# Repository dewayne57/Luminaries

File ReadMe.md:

# Luminaries 

This project contains the software and hardware for simulated candles that operate from 12V 
(meaning they can be powered from lawn lighting) with optional CDS (Cadmium-Sulfide) photo
cell control (on at dusk off at dawn).  The software simulates a fairly large candle, like 
might be placed inside a luminary or pumpkin.

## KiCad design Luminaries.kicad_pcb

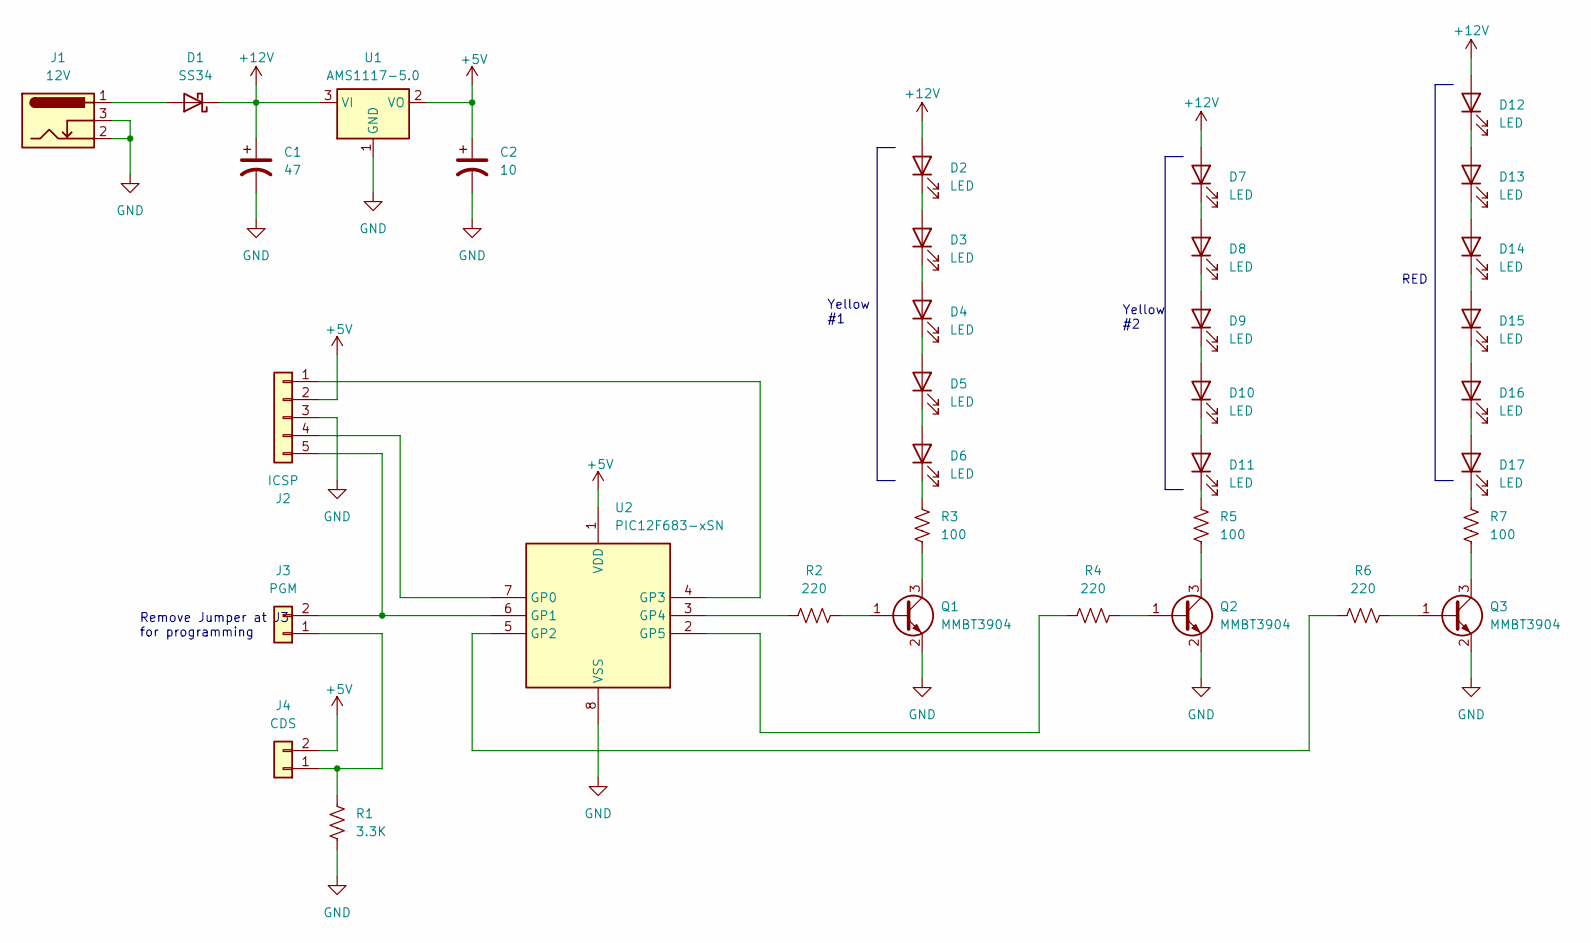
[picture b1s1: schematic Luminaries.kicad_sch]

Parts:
C1: 47; CP_Elec_10x10
C2: 10; CP_Elec_4x3
D1: SS34; D_SMA
D2, D3, D4, D5, D6, D7, D8, D9, D10, D11, D12, D13, D14, D15, D16, D17: LED; LED_D5.0mm_IRGrey
J1: 12V; BarrelJack_Horizontal
J2: ICSP; PinHeader_1x05_P2.54mm_Vertical
J3: PGM; PinHeader_1x02_P2.54mm_Vertical
J4: CDS; PinHeader_1x02_P2.54mm_Vertical
Q1, Q2, Q3: MMBT3904; SOT-23
R1: 3.3K; R_0805_2012Metric_Pad1.20x1.40mm_HandSolder
R2, R4, R6: 220; R_0805_2012Metric_Pad1.20x1.40mm_HandSolder
R3, R5, R7: 100; R_0805_2012Metric_Pad1.20x1.40mm_HandSolder
U1: AMS1117-5.0; SOT-223-3_TabPin2
U2: PIC12F683-xSN; SOIC-8_3.9x4.9mm_P1.27mm

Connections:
+5V: C2.1, J2.2, J4.2, U1.2 (VO), U2.1 (VDD)
+12V: C1.1, D1.1 (K), D2.2 (A), D7.2 (A), D12.2 (A), U1.3 (VI)
GND: C1.2, C2.2, J1.2, J1.3, J2.3, Q1.2 (E), Q2.2 (E), Q3.2 (E), R1.2, U1.1 (GND), U2.8 (VSS)
unnamed: D1.2 (A), J1.1
unnamed: D2.1 (K), D3.2 (A)
unnamed: D3.1 (K), D4.2 (A)
unnamed: D4.1 (K), D5.2 (A)
unnamed: D5.1 (K), D6.2 (A)
unnamed: D6.1 (K), R3.2
unnamed: D7.1 (K), D8.2 (A)
unnamed: D8.1 (K), D9.2 (A)
unnamed: D9.1 (K), D10.2 (A)
unnamed: D10.1 (K), D11.2 (A)
unnamed: D11.1 (K), R5.2
unnamed: D12.1 (K), D13.2 (A)
unnamed: D13.1 (K), D14.2 (A)
unnamed: D14.1 (K), D15.2 (A)
unnamed: D15.1 (K), D16.2 (A)
unnamed: D16.1 (K), D17.2 (A)
unnamed: D17.1 (K), R7.2
unnamed: J2.1, U2.4 (GP3)
unnamed: J2.4, U2.7 (GP0)
unnamed: J2.5, J3.2, U2.6 (GP1)
unnamed: J3.1, J4.1, R1.1
unnamed: Q1.1 (B), R2.2
unnamed: Q1.3 (C), R3.1
unnamed: Q2.1 (B), R4.2
unnamed: Q2.3 (C), R5.1
unnamed: Q3.1 (B), R6.2
unnamed: Q3.3 (C), R7.1
unnamed: R6.1, U2.5 (GP2)
unnamed: R2.1, U2.3 (GP4)
unnamed: R4.1, U2.2 (GP5)

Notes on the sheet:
RED
Yellow #1
Remove Jumper at J3 for programming
Yellow #2

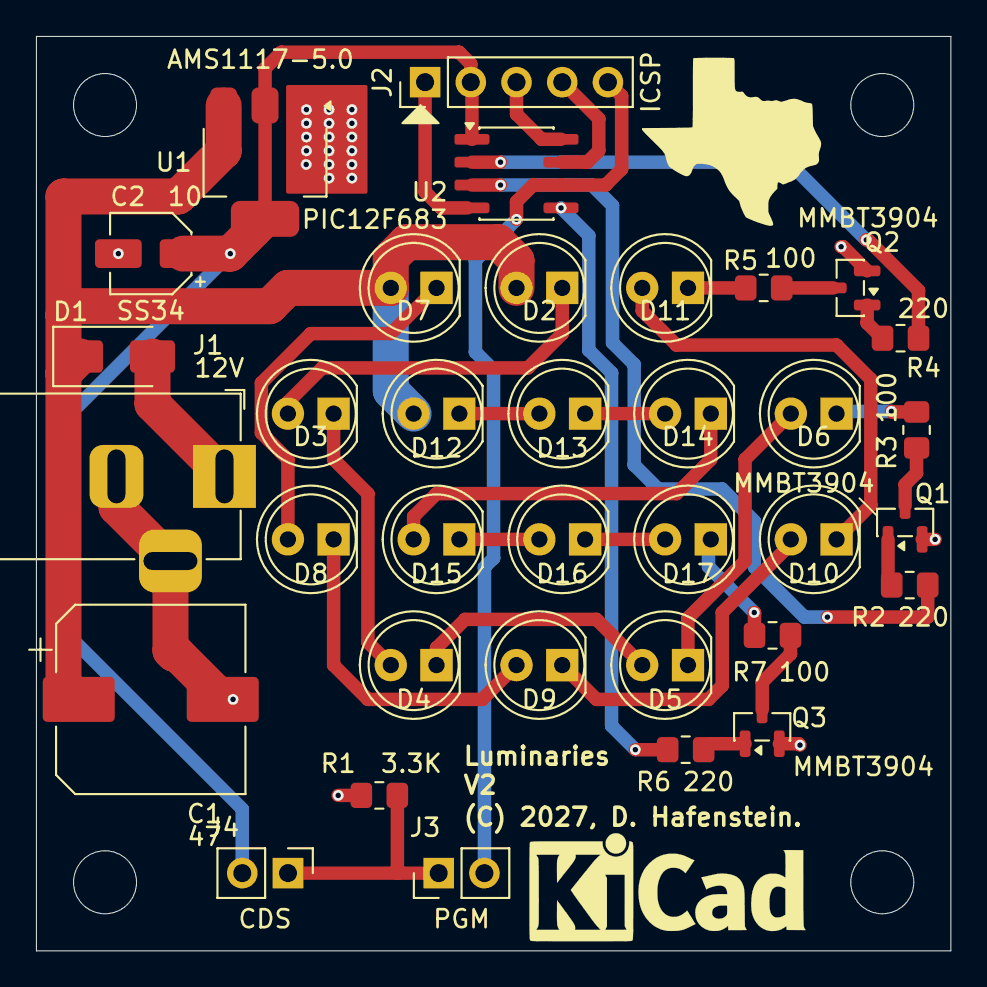
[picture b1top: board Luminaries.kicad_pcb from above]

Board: 2 copper layers, 50.8 x 50.8 mm, 35 parts (0 on the bottom side), 33 nets.

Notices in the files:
Luminaries.kicad_pcb:
(C) 2027, D. Hafenstein.
